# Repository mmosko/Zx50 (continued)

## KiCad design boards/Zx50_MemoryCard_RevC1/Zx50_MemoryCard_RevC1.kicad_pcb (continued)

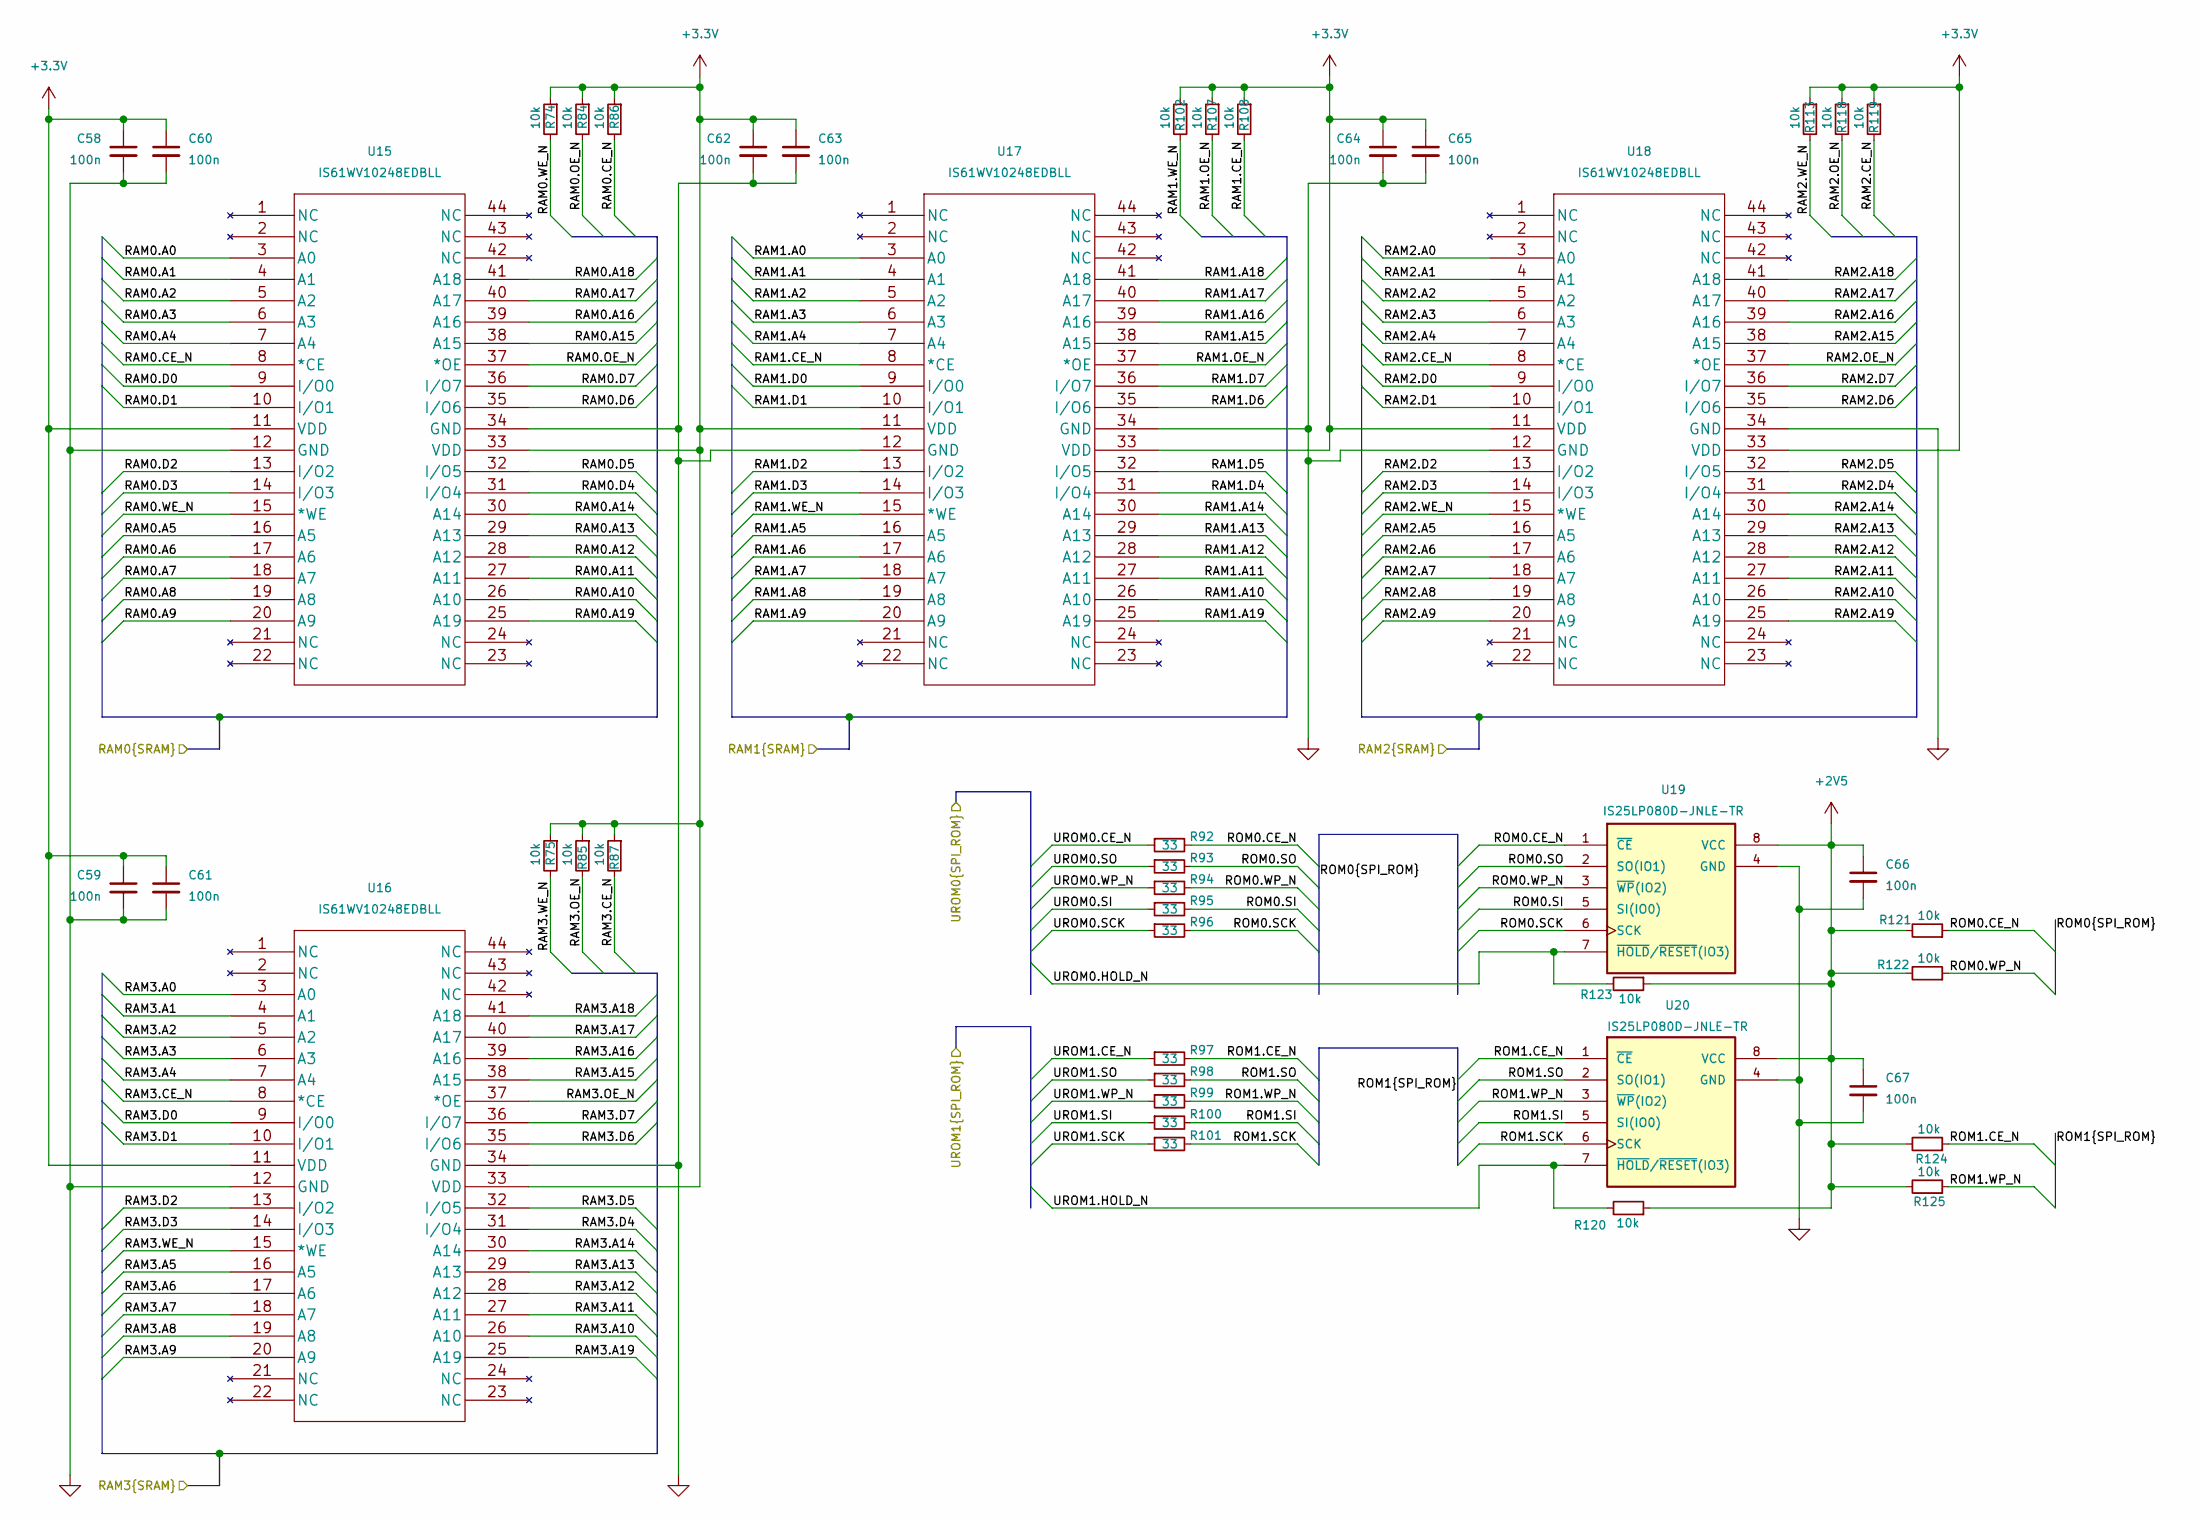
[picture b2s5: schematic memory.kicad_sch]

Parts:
C58, C59, C60, C61, C62, C63, C64, C65, C66, C67: 100n; C_0402_1005Metric; LCSC C1525
R74, R75, R84, R85, R86, R87, R102, R107, R108, R113, R118, R119, R120, R121, R122, R123, R124, R125: 10k; R_0402_1005Metric; MFG_PN 0402WGF1002TCE; LCSC C25744
R92, R93, R94, R95, R96, R97, R98, R99, R100, R101: 33; R_0402_1005Metric; MFG_PN 0402WGF1000TCE; LCSC C25076
U15, U16, U17, U18: IS61WV10248EDBLL; TSOP-44_11P9X18P5_ISI; LCSC C1349228
U19, U20: IS25LP080D-JNLE-TR; SOIC127P600X88-8N; DigiKey_PN 706-1581-1-ND

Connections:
+2V5: C66.1, C67.1, R120.1, R121.2, R122.2, R123.1, R124.2, R125.2, U19.8 (VCC), U20.8 (VCC); also elsewhere on the board
+3.3V: C58.1, C59.1, C60.1, C61.1, C62.1, C63.1, C64.1, C65.1, R74.1, R75.1, R84.1, R85.1, R86.1, R87.1, R102.1, R107.1, R108.1, R113.1, R118.1, R119.1, U15.11 (VDD), U15.33 (VDD), U16.11 (VDD), U16.33 (VDD), U17.11 (VDD), U17.33 (VDD), U18.11 (VDD), U18.33 (VDD); also elsewhere on the board
/FPGA/RAM0.A0: U15.3 (A0); also elsewhere on the board
/FPGA/RAM0.A1: U15.4 (A1); also elsewhere on the board
/FPGA/RAM0.A2: U15.5 (A2); also elsewhere on the board
/FPGA/RAM0.A3: U15.6 (A3); also elsewhere on the board
/FPGA/RAM0.A4: U15.7 (A4); also elsewhere on the board
/FPGA/RAM0.A5: U15.16 (A5); also elsewhere on the board
/FPGA/RAM0.A6: U15.17 (A6); also elsewhere on the board
/FPGA/RAM0.A7: U15.18 (A7); also elsewhere on the board
/FPGA/RAM0.A8: U15.19 (A8); also elsewhere on the board
/FPGA/RAM0.A9: U15.20 (A9); also elsewhere on the board
/FPGA/RAM0.A10: U15.26 (A10); also elsewhere on the board
/FPGA/RAM0.A11: U15.27 (A11); also elsewhere on the board
/FPGA/RAM0.A12: U15.28 (A12); also elsewhere on the board
/FPGA/RAM0.A13: U15.29 (A13); also elsewhere on the board
/FPGA/RAM0.A14: U15.30 (A14); also elsewhere on the board
/FPGA/RAM0.A15: U15.38 (A15); also elsewhere on the board
/FPGA/RAM0.A16: U15.39 (A16); also elsewhere on the board
/FPGA/RAM0.A17: U15.40 (A17); also elsewhere on the board
/FPGA/RAM0.A18: U15.41 (A18); also elsewhere on the board
/FPGA/RAM0.A19: U15.25 (A19); also elsewhere on the board
/FPGA/RAM0.CE_N: R86.2, U15.8 (*CE); also elsewhere on the board
/FPGA/RAM0.D0: U15.9 (I/O0); also elsewhere on the board
/FPGA/RAM0.D1: U15.10 (I/O1); also elsewhere on the board
/FPGA/RAM0.D2: U15.13 (I/O2); also elsewhere on the board
/FPGA/RAM0.D3: U15.14 (I/O3); also elsewhere on the board
/FPGA/RAM0.D4: U15.31 (I/O4); also elsewhere on the board
/FPGA/RAM0.D5: U15.32 (I/O5); also elsewhere on the board
/FPGA/RAM0.D6: U15.35 (I/O6); also elsewhere on the board
/FPGA/RAM0.D7: U15.36 (I/O7); also elsewhere on the board
/FPGA/RAM0.OE_N: R84.2, U15.37 (*OE); also elsewhere on the board
/FPGA/RAM0.WE_N: R74.2, U15.15 (*WE); also elsewhere on the board
/FPGA/RAM1.A0: U17.3 (A0); also elsewhere on the board
/FPGA/RAM1.A1: U17.4 (A1); also elsewhere on the board
/FPGA/RAM1.A2: U17.5 (A2); also elsewhere on the board
/FPGA/RAM1.A3: U17.6 (A3); also elsewhere on the board
/FPGA/RAM1.A4: U17.7 (A4); also elsewhere on the board
/FPGA/RAM1.A5: U17.16 (A5); also elsewhere on the board
/FPGA/RAM1.A6: U17.17 (A6); also elsewhere on the board
/FPGA/RAM1.A7: U17.18 (A7); also elsewhere on the board
/FPGA/RAM1.A8: U17.19 (A8); also elsewhere on the board
/FPGA/RAM1.A9: U17.20 (A9); also elsewhere on the board
/FPGA/RAM1.A10: U17.26 (A10); also elsewhere on the board
/FPGA/RAM1.A11: U17.27 (A11); also elsewhere on the board
/FPGA/RAM1.A12: U17.28 (A12); also elsewhere on the board
/FPGA/RAM1.A13: U17.29 (A13); also elsewhere on the board
/FPGA/RAM1.A14: U17.30 (A14); also elsewhere on the board
/FPGA/RAM1.A15: U17.38 (A15); also elsewhere on the board
/FPGA/RAM1.A16: U17.39 (A16); also elsewhere on the board
/FPGA/RAM1.A17: U17.40 (A17); also elsewhere on the board
/FPGA/RAM1.A18: U17.41 (A18); also elsewhere on the board
/FPGA/RAM1.A19: U17.25 (A19); also elsewhere on the board
/FPGA/RAM1.CE_N: R108.2, U17.8 (*CE); also elsewhere on the board
/FPGA/RAM1.D0: U17.9 (I/O0); also elsewhere on the board
/FPGA/RAM1.D1: U17.10 (I/O1); also elsewhere on the board
/FPGA/RAM1.D2: U17.13 (I/O2); also elsewhere on the board
/FPGA/RAM1.D3: U17.14 (I/O3); also elsewhere on the board
/FPGA/RAM1.D4: U17.31 (I/O4); also elsewhere on the board
/FPGA/RAM1.D5: U17.32 (I/O5); also elsewhere on the board
/FPGA/RAM1.D6: U17.35 (I/O6); also elsewhere on the board
/FPGA/RAM1.D7: U17.36 (I/O7); also elsewhere on the board
/FPGA/RAM1.OE_N: R107.2, U17.37 (*OE); also elsewhere on the board
/FPGA/RAM1.WE_N: R102.2, U17.15 (*WE); also elsewhere on the board
/FPGA/RAM2.A0: U18.3 (A0); also elsewhere on the board
/FPGA/RAM2.A1: U18.4 (A1); also elsewhere on the board
/FPGA/RAM2.A2: U18.5 (A2); also elsewhere on the board
/FPGA/RAM2.A3: U18.6 (A3); also elsewhere on the board
/FPGA/RAM2.A4: U18.7 (A4); also elsewhere on the board
/FPGA/RAM2.A5: U18.16 (A5); also elsewhere on the board
/FPGA/RAM2.A6: U18.17 (A6); also elsewhere on the board
/FPGA/RAM2.A7: U18.18 (A7); also elsewhere on the board
/FPGA/RAM2.A8: U18.19 (A8); also elsewhere on the board
/FPGA/RAM2.A9: U18.20 (A9); also elsewhere on the board
/FPGA/RAM2.A10: U18.26 (A10); also elsewhere on the board
/FPGA/RAM2.A11: U18.27 (A11); also elsewhere on the board
/FPGA/RAM2.A12: U18.28 (A12); also elsewhere on the board
/FPGA/RAM2.A13: U18.29 (A13); also elsewhere on the board
/FPGA/RAM2.A14: U18.30 (A14); also elsewhere on the board
/FPGA/RAM2.A15: U18.38 (A15); also elsewhere on the board
/FPGA/RAM2.A16: U18.39 (A16); also elsewhere on the board
/FPGA/RAM2.A17: U18.40 (A17); also elsewhere on the board
/FPGA/RAM2.A18: U18.41 (A18); also elsewhere on the board
/FPGA/RAM2.A19: U18.25 (A19); also elsewhere on the board
/FPGA/RAM2.CE_N: R119.2, U18.8 (*CE); also elsewhere on the board
/FPGA/RAM2.D0: U18.9 (I/O0); also elsewhere on the board
/FPGA/RAM2.D1: U18.10 (I/O1); also elsewhere on the board
/FPGA/RAM2.D2: U18.13 (I/O2); also elsewhere on the board
/FPGA/RAM2.D3: U18.14 (I/O3); also elsewhere on the board
/FPGA/RAM2.D4: U18.31 (I/O4); also elsewhere on the board
/FPGA/RAM2.D5: U18.32 (I/O5); also elsewhere on the board
/FPGA/RAM2.D6: U18.35 (I/O6); also elsewhere on the board
/FPGA/RAM2.D7: U18.36 (I/O7); also elsewhere on the board
/FPGA/RAM2.OE_N: R118.2, U18.37 (*OE); also elsewhere on the board
/FPGA/RAM2.WE_N: R113.2, U18.15 (*WE); also elsewhere on the board
/FPGA/RAM3.A0: U16.3 (A0); also elsewhere on the board
/FPGA/RAM3.A1: U16.4 (A1); also elsewhere on the board
/FPGA/RAM3.A2: U16.5 (A2); also elsewhere on the board
/FPGA/RAM3.A3: U16.6 (A3); also elsewhere on the board
/FPGA/RAM3.A4: U16.7 (A4); also elsewhere on the board
/FPGA/RAM3.A5: U16.16 (A5); also elsewhere on the board
/FPGA/RAM3.A6: U16.17 (A6); also elsewhere on the board
/FPGA/RAM3.A7: U16.18 (A7); also elsewhere on the board
/FPGA/RAM3.A8: U16.19 (A8); also elsewhere on the board
/FPGA/RAM3.A9: U16.20 (A9); also elsewhere on the board
/FPGA/RAM3.A10: U16.26 (A10); also elsewhere on the board
/FPGA/RAM3.A11: U16.27 (A11); also elsewhere on the board
/FPGA/RAM3.A12: U16.28 (A12); also elsewhere on the board
/FPGA/RAM3.A13: U16.29 (A13); also elsewhere on the board
/FPGA/RAM3.A14: U16.30 (A14); also elsewhere on the board
/FPGA/RAM3.A15: U16.38 (A15); also elsewhere on the board
/FPGA/RAM3.A16: U16.39 (A16); also elsewhere on the board
/FPGA/RAM3.A17: U16.40 (A17); also elsewhere on the board
/FPGA/RAM3.A18: U16.41 (A18); also elsewhere on the board
/FPGA/RAM3.A19: U16.25 (A19); also elsewhere on the board
/FPGA/RAM3.CE_N: R87.2, U16.8 (*CE); also elsewhere on the board
/FPGA/RAM3.D0: U16.9 (I/O0); also elsewhere on the board
/FPGA/RAM3.D1: U16.10 (I/O1); also elsewhere on the board
/FPGA/RAM3.D2: U16.13 (I/O2); also elsewhere on the board
/FPGA/RAM3.D3: U16.14 (I/O3); also elsewhere on the board
/FPGA/RAM3.D4: U16.31 (I/O4); also elsewhere on the board
/FPGA/RAM3.D5: U16.32 (I/O5); also elsewhere on the board
/FPGA/RAM3.D6: U16.35 (I/O6); also elsewhere on the board
/FPGA/RAM3.D7: U16.36 (I/O7); also elsewhere on the board
/FPGA/RAM3.OE_N: R85.2, U16.37 (*OE); also elsewhere on the board
/FPGA/RAM3.WE_N: R75.2, U16.15 (*WE); also elsewhere on the board
/FPGA/UROM0.CE_N: R92.1; also elsewhere on the board
/FPGA/UROM0.HOLD_N: R123.2, U19.7 (~HOLD/~RESET(IO3)); also elsewhere on the board
/FPGA/UROM0.SCK: R96.1; also elsewhere on the board
/FPGA/UROM0.SI: R95.1; also elsewhere on the board
/FPGA/UROM0.SO: R93.1; also elsewhere on the board
/FPGA/UROM0.WP_N: R94.1; also elsewhere on the board
/FPGA/UROM1.CE_N: R97.1; also elsewhere on the board
/FPGA/UROM1.HOLD_N: R120.2, U20.7 (~HOLD/~RESET(IO3)); also elsewhere on the board
/FPGA/UROM1.SCK: R101.1; also elsewhere on the board
/FPGA/UROM1.SI: R100.1; also elsewhere on the board
/FPGA/UROM1.SO: R98.1; also elsewhere on the board
/FPGA/UROM1.WP_N: R99.1; also elsewhere on the board
/FPGA/memory/ROM0.CE_N: R92.2, R121.1, U19.1 (~CE)
/FPGA/memory/ROM0.SCK: R96.2, U19.6 (SCK)
/FPGA/memory/ROM0.SI: R95.2, U19.5 (SI(IO0))
/FPGA/memory/ROM0.SO: R93.2, U19.2 (SO(IO1))
/FPGA/memory/ROM0.WP_N: R94.2, R122.1, U19.3 (~WP(IO2))
/FPGA/memory/ROM1.CE_N: R97.2, R124.1, U20.1 (~CE)
/FPGA/memory/ROM1.SCK: R101.2, U20.6 (SCK)
/FPGA/memory/ROM1.SI: R100.2, U20.5 (SI(IO0))
/FPGA/memory/ROM1.SO: R98.2, U20.2 (SO(IO1))
/FPGA/memory/ROM1.WP_N: R99.2, R125.1, U20.3 (~WP(IO2))
GND: C58.2, C59.2, C60.2, C61.2, C62.2, C63.2, C64.2, C65.2, C66.2, C67.2, U15.12 (GND), U15.34 (GND), U16.12 (GND), U16.34 (GND), U17.12 (GND), U17.34 (GND), U18.12 (GND), U18.34 (GND), U19.4 (GND), U20.4 (GND); also elsewhere on the board

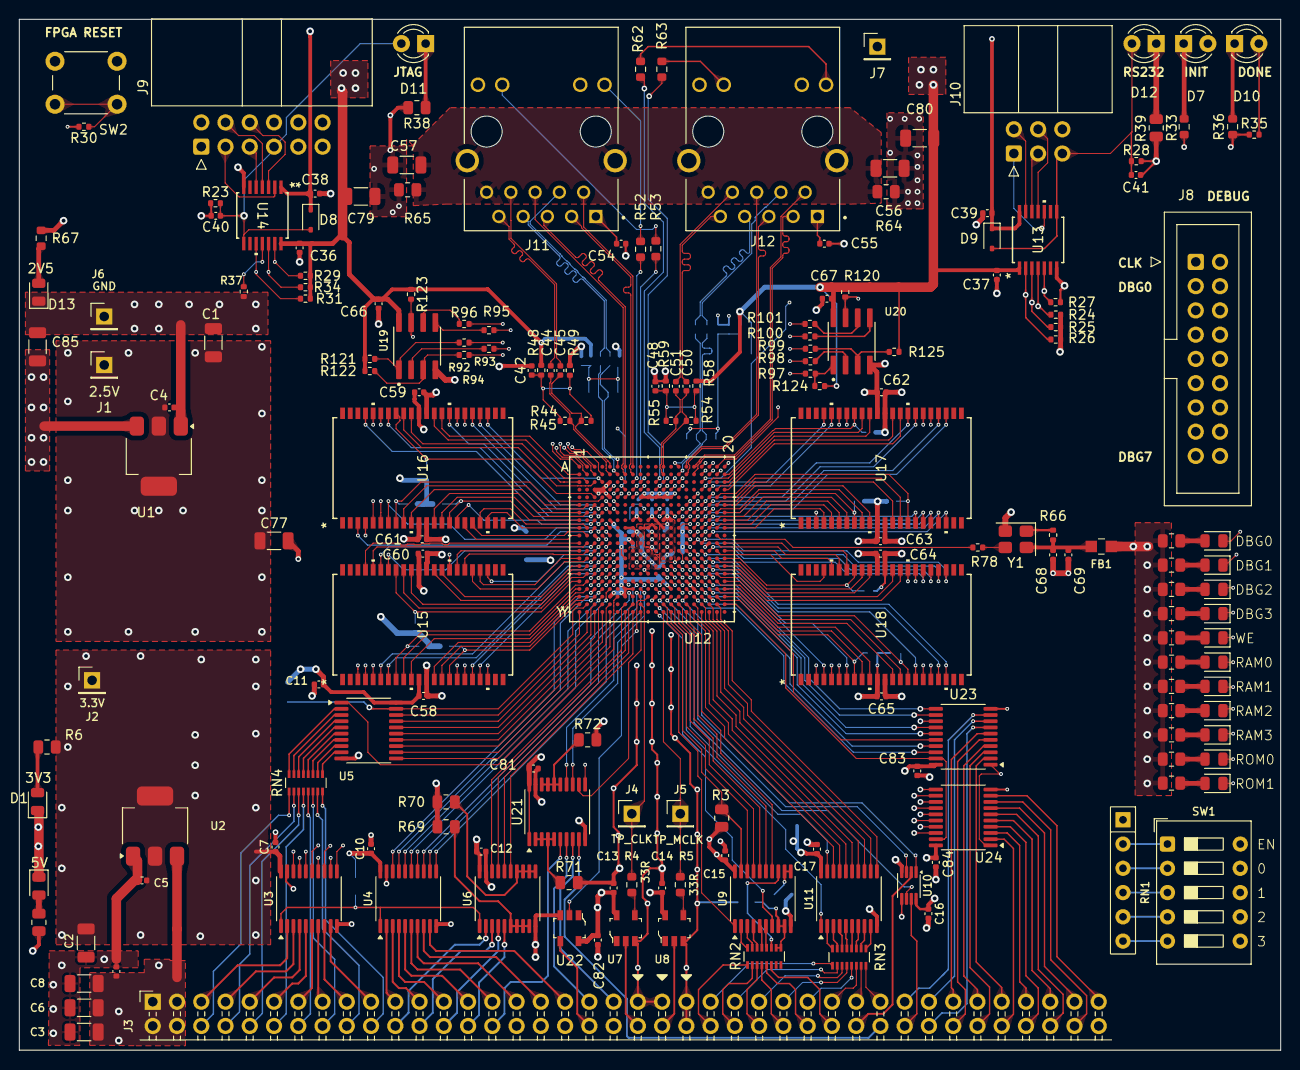
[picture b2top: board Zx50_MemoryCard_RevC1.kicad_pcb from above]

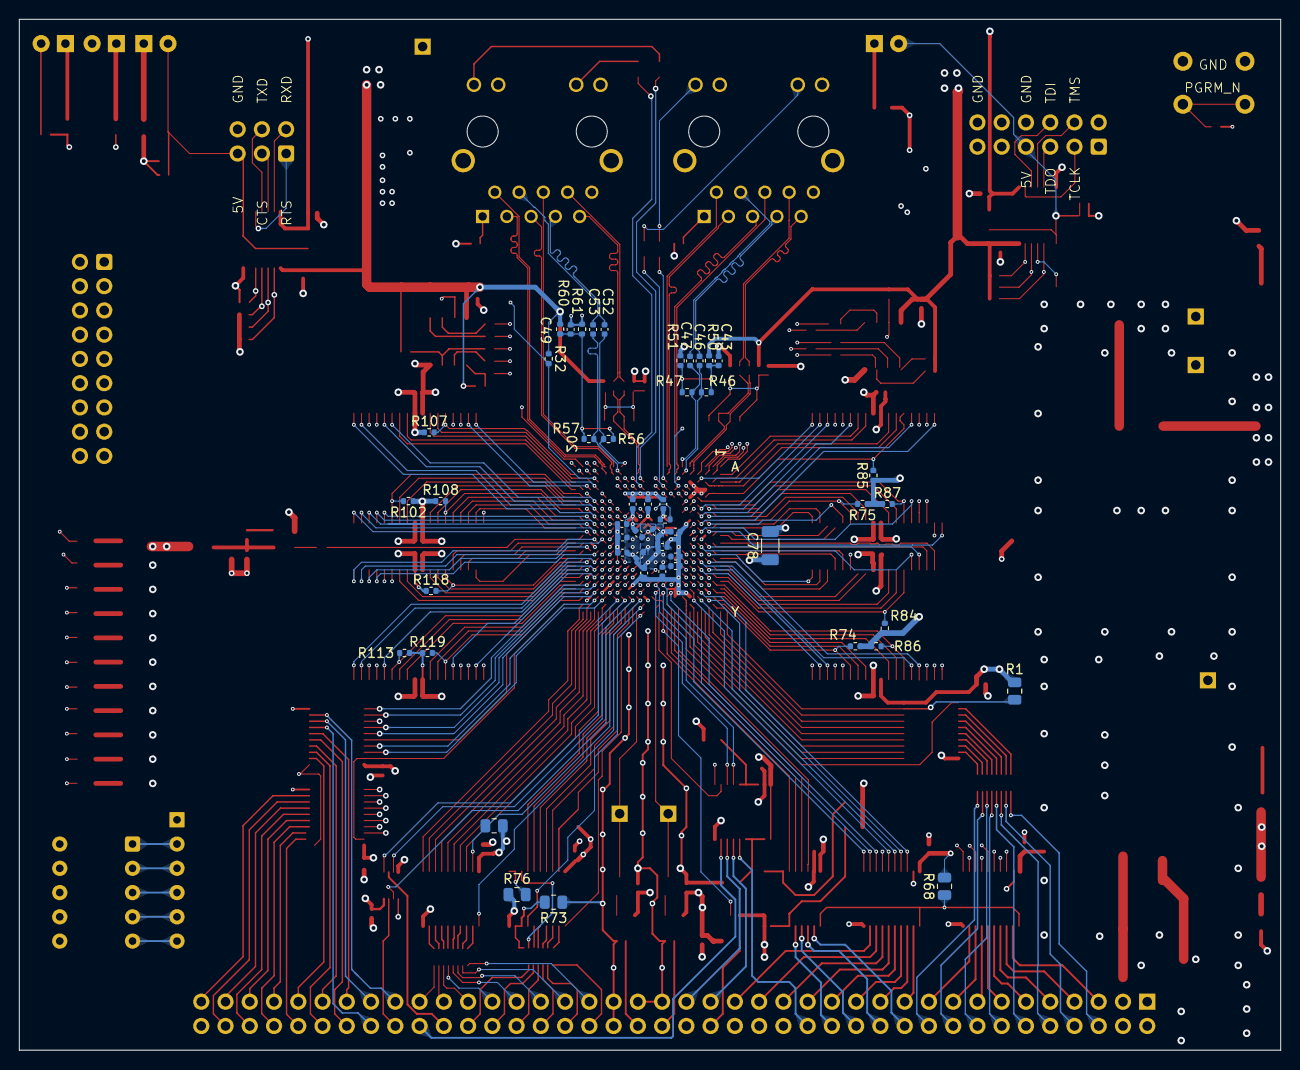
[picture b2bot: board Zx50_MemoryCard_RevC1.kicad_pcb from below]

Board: 6 copper layers, 132.1 x 107.9 mm, 235 parts (49 on the bottom side), 433 nets.

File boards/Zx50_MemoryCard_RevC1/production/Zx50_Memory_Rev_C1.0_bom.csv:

Designator,Footprint,Quantity,Value,LCSC Part #
"C1, C2, C3, C6, C77, C78, C79, C8, C80, C85",1206,10,10u,C7171
"C10, C11, C12, C13, C14, C15, C16, C17, C18, C22, C23, C24, C28, C29, C30, C31, C32, C33, C34, C35, C36, C37, C38, C39, C4, C40, C41, C42, C43, C48, C49, C5, C54, C58, C59, C60, C61, C62, C63, C64, C65, C66, C67, C68, C7, C74, C75, C76, C81, C82, C83, C84, C9",0402,53,100n,C1525
"C44, C45, C46, C47, C50, C51, C52, C53",0402,8,220nF,C16772
C55,0402,1,200n,C1525
"C56, C57",1206,2,1n 2kV,C9196
C69,0402,1,1uF,C52923
D10,LED_D3.0mm,1,DONE,
D11,LED_D3.0mm,1,JTAG ACT,
D12,LED_D3.0mm,1,RS232 ACT,
D7,LED_D3.0mm,1,INIT,
"D8, D9",D_SOD-323,2,1N5819,C191023
FB1,0805,1,600R,C1017
J1,PinHeader_1x01_P2.54mm_Vertical,1,2.5V,
J10,IDC-Header_2x03_P2.54mm_Horizontal,1,RS232 5V,
"J11, J12",HANRUN_HR911130A,2,RJ45_RB1-125B8G1A,C50933
J2,PinHeader_1x01_P2.54mm_Vertical,1,3.3V,
J3,PinSocket_2x40_P2.54mm_Horizontal_Edge,1,Zx50_EdgeConnector,
J4,PinHeader_1x01_P2.54mm_Vertical,1,TP_CLK,
J5,PinHeader_1x01_P2.54mm_Vertical,1,TP_MCLK,
"J6, J7",PinHeader_1x01_P2.54mm_Vertical,2,GND,
J8,IDC-Header_2x09_P2.54mm_Vertical,1,DEBUG,
J9,IDC-Header_2x06_P2.54mm_Horizontal,1,JTAG 5V,
"R1, R2, R3, R68, R69, R70, R71, R72, R73, R76",0805,10,10k,C17414
"R102, R107, R108, R113, R118, R119, R120, R121, R122, R123, R124, R125, R23, R28, R30, R32, R35, R40, R66, R74, R75, R84, R85, R86, R87",0402,25,10k,C25744
"R24, R25, R26, R27, R29, R31, R34, R37",0402,8,4k7,C25900
"R38, R39",0805,2,470R,C17710
"R4, R5",0603,2,33R,C23140
RN1,R_Array_SIP6,1,10K,	 4606X-AP1-103LF
"RN2, RN3, RN4",R_Array_Convex_8x0602,3,33R,C422182
SW1,SW_DIP_SPSTx05_Slide_9.78x14.88mm_W7.62mm_P2.54mm,1,SW_DIP_x05,208-5
U1,SOT-223-3_TabPin2,1,AMS1117-2.5,C347221
U10,VSSOP-8_2.3x2mm_P0.5mm,1,74LVC3G07,C131955
"U11, U21, U23, U24, U3, U4, U5, U6, U9",TSSOP-20_4.4x6.5mm_P0.65mm,9,74LVC245,C7848
U12,CABGA400_LAT,1,LCMXO3LF-6900C-5BG400C,
U13,TSSOP14_PW_TEX,1,TXU0204PWR,C4363888
U14,TSSOP14_PW_TEX,1,TXU0304PWR,C4364118
"U15, U16, U17, U18",TSOP-44_11P9X18P5_ISI,4,IS61WV10248EDBLL,C1349228
"U19, U20",SOIC127P600X88-8N,2,IS25LP080D-JNLE-TR,C521286
U2,SOT-223-3_TabPin2,1,AMS1117-3.3,C6186
U22,SOT-753,1,SN74LVC1G17DBVR,SN74LVC1G17DBVR
"U7, U8",SOT-753,2,74LVC1G17,C7836
Y1,Crystal_SMD_3225-4Pin_3.2x2.5mm,1,25 MHz,C669088
